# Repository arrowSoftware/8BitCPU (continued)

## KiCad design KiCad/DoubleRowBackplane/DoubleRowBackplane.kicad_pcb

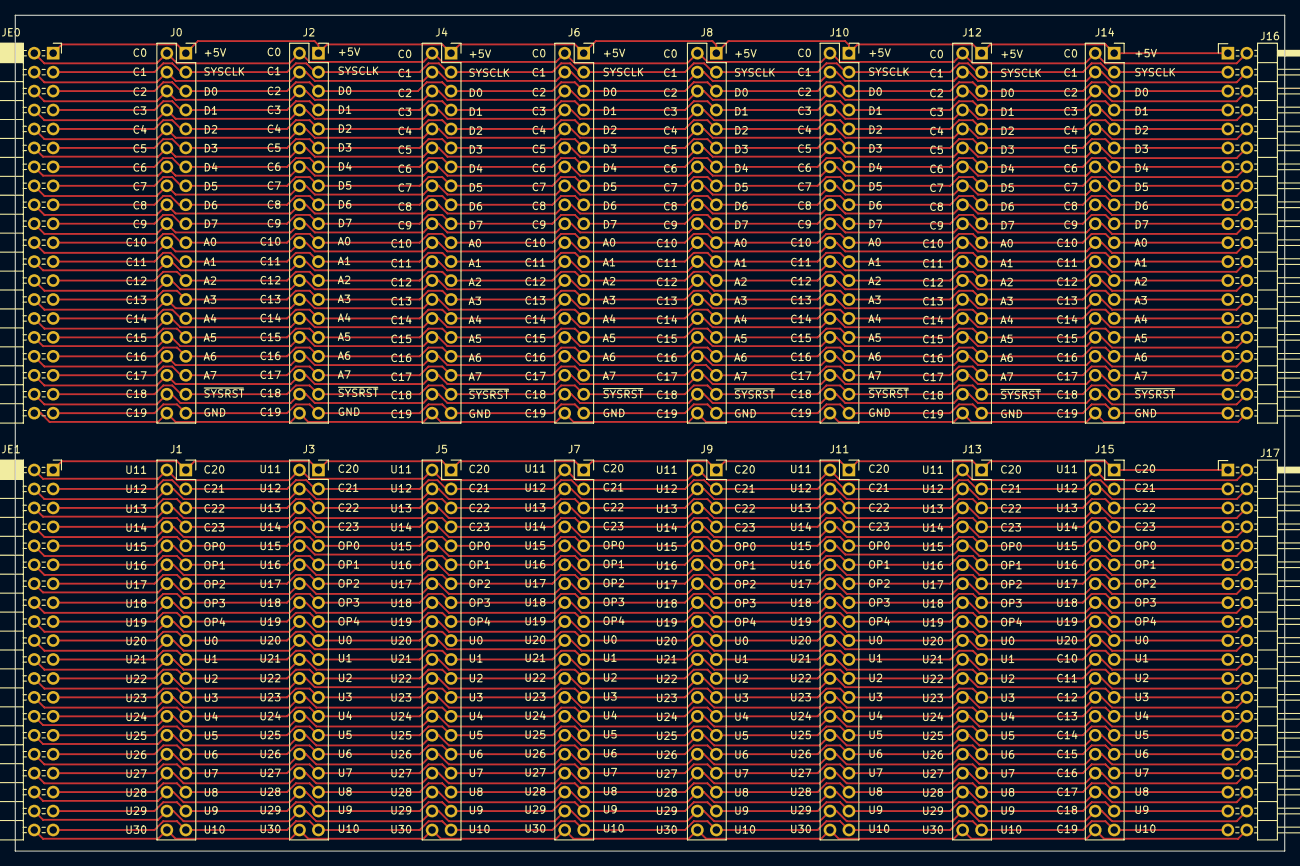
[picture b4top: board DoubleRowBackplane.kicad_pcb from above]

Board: 2 copper layers, 170.2 x 112.0 mm, 20 parts (0 on the bottom side), 80 nets.

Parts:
J0, J1, J2, J3, J4, J5, J6, J7, J8, J9, J10, J11, J12, J13, J14, J15: Conn_02x20_Row_Letter_First; PinSocket_2x20_P2.54mm_Vertical
J16, J17: Conn_02x20_Row_Letter_First; PinHeader_2x20_P2.54mm_Horizontal
JE0, JE1: Conn_02x20_Row_Letter_First; PinSocket_2x20_P2.54mm_Horizontal

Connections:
/+5V: J0.1, J2.1, J4.1, J6.1, J8.1, J10.1, J12.1, J14.1, J16.1, JE0.1
/A0: J0.21, J2.21, J4.21, J6.21, J8.21, J10.21, J12.21, J14.21, J16.21, JE0.21
/A1: J0.23, J2.23, J4.23, J6.23, J8.23, J10.23, J12.23, J14.23, J16.23, JE0.23
/A2: J0.25, J2.25, J4.25, J6.25, J8.25, J10.25, J12.25, J14.25, J16.25, JE0.25
/A3: J0.27, J2.27, J4.27, J6.27, J8.27, J10.27, J12.27, J14.27, J16.27, JE0.27
/A4: J0.29, J2.29, J4.29, J6.29, J8.29, J10.29, J12.29, J14.29, J16.29, JE0.29
/A5: J0.31, J2.31, J4.31, J6.31, J8.31, J10.31, J12.31, J14.31, J16.31, JE0.31
/A6: J0.33, J2.33, J4.33, J6.33, J8.33, J10.33, J12.33, J14.33, J16.33, JE0.33
/A7: J0.35, J2.35, J4.35, J6.35, J8.35, J10.35, J12.35, J14.35, J16.35, JE0.35
/C0: J0.2, J2.2, J4.2, J6.2, J8.2, J10.2, J12.2, J14.2, J16.2, JE0.2
/C1: J0.4, J2.4, J4.4, J6.4, J8.4, J10.4, J12.4, J14.4, J16.4, JE0.4
/C2: J0.6, J2.6, J4.6, J6.6, J8.6, J10.6, J12.6, J14.6, J16.6, JE0.6
/C3: J0.8, J2.8, J4.8, J6.8, J8.8, J10.8, J12.8, J14.8, J16.8, JE0.8
/C4: J0.10, J2.10, J4.10, J6.10, J8.10, J10.10, J12.10, J14.10, J16.10, JE0.10
/C5: J0.12, J2.12, J4.12, J6.12, J8.12, J10.12, J12.12, J14.12, J16.12, JE0.12
/C6: J0.14, J2.14, J4.14, J6.14, J8.14, J10.14, J12.14, J14.14, J16.14, JE0.14
/C7: J0.16, J2.16, J4.16, J6.16, J8.16, J10.16, J12.16, J14.16, J16.16, JE0.16
/C8: J0.18, J2.18, J4.18, J6.18, J8.18, J10.18, J12.18, J14.18, J16.18, JE0.18
/C9: J0.20, J2.20, J4.20, J6.20, J8.20, J10.20, J12.20, J14.20, J16.20, JE0.20
/C10: J0.22, J2.22, J4.22, J6.22, J8.22, J10.22, J12.22, J14.22, J16.22, JE0.22
/C11: J0.24, J2.24, J4.24, J6.24, J8.24, J10.24, J12.24, J14.24, J16.24, JE0.24
/C12: J0.26, J2.26, J4.26, J6.26, J8.26, J10.26, J12.26, J14.26, J16.26, JE0.26
/C13: J0.28, J2.28, J4.28, J6.28, J8.28, J10.28, J12.28, J14.28, J16.28, JE0.28
/C14: J0.30, J2.30, J4.30, J6.30, J8.30, J10.30, J12.30, J14.30, J16.30, JE0.30
/C15: J0.32, J2.32, J4.32, J6.32, J8.32, J10.32, J12.32, J14.32, J16.32, JE0.32
/C16: J0.34, J2.34, J4.34, J6.34, J8.34, J10.34, J12.34, J14.34, J16.34, JE0.34
/C17: J0.36, J2.36, J4.36, J6.36, J8.36, J10.36, J12.36, J14.36, J16.36, JE0.36
/C18: J0.38, J2.38, J4.38, J6.38, J8.38, J10.38, J12.38, J14.38, J16.38, JE0.38
/C19: J0.40, J2.40, J4.40, J6.40, J8.40, J10.40, J12.40, J14.40, J16.40, JE0.40
/C20: J1.1, J3.1, J5.1, J7.1, J9.1, J11.1, J13.1, J15.1, J17.1, JE1.1
/C21: J1.3, J3.3, J5.3, J7.3, J9.3, J11.3, J13.3, J15.3, J17.3, JE1.3
/C22: J1.5, J3.5, J5.5, J7.5, J9.5, J11.5, J13.5, J15.5, J17.5, JE1.5
/C23: J1.7, J3.7, J5.7, J7.7, J9.7, J11.7, J13.7, J15.7, J17.7, JE1.7
/D0: J0.5, J2.5, J4.5, J6.5, J8.5, J10.5, J12.5, J14.5, J16.5, JE0.5
/D1: J0.7, J2.7, J4.7, J6.7, J8.7, J10.7, J12.7, J14.7, J16.7, JE0.7
/D2: J0.9, J2.9, J4.9, J6.9, J8.9, J10.9, J12.9, J14.9, J16.9, JE0.9
/D3: J0.11, J2.11, J4.11, J6.11, J8.11, J10.11, J12.11, J14.11, J16.11, JE0.11
/D4: J0.13, J2.13, J4.13, J6.13, J8.13, J10.13, J12.13, J14.13, J16.13, JE0.13
/D5: J0.15, J2.15, J4.15, J6.15, J8.15, J10.15, J12.15, J14.15, J16.15, JE0.15
/D6: J0.17, J2.17, J4.17, J6.17, J8.17, J10.17, J12.17, J14.17, J16.17, JE0.17
/D7: J0.19, J2.19, J4.19, J6.19, J8.19, J10.19, J12.19, J14.19, J16.19, JE0.19
/GND: J0.39, J2.39, J4.39, J6.39, J8.39, J10.39, J12.39, J14.39, J16.39, JE0.39
/OP0: J1.9, J3.9, J5.9, J7.9, J9.9, J11.9, J13.9, J15.9, J17.9, JE1.9
/OP1: J1.11, J3.11, J5.11, J7.11, J9.11, J11.11, J13.11, J15.11, J17.11, JE1.11
/OP2: J1.13, J3.13, J5.13, J7.13, J9.13, J11.13, J13.13, J15.13, J17.13, JE1.13
/OP3: J1.15, J3.15, J5.15, J7.15, J9.15, J11.15, J13.15, J15.15, J17.15, JE1.15
/OP4: J1.17, J3.17, J5.17, J7.17, J9.17, J11.17, J13.17, J15.17, J17.17, JE1.17
/SYSCLK: J0.3, J2.3, J4.3, J6.3, J8.3, J10.3, J12.3, J14.3, J16.3, JE0.3
/U0: J1.19, J3.19, J5.19, J7.19, J9.19, J11.19, J13.19, J15.19, J17.19, JE1.19
/U1: J1.21, J3.21, J5.21, J7.21, J9.21, J11.21, J13.21, J15.21, J17.21, JE1.21
/U2: J1.23, J3.23, J5.23, J7.23, J9.23, J11.23, J13.23, J15.23, J17.23, JE1.23
/U3: J1.25, J3.25, J5.25, J7.25, J9.25, J11.25, J13.25, J15.25, J17.25, JE1.25
/U4: J1.27, J3.27, J5.27, J7.27, J9.27, J11.27, J13.27, J15.27, J17.27, JE1.27
/U5: J1.29, J3.29, J5.29, J7.29, J9.29, J11.29, J13.29, J15.29, J17.29, JE1.29
/U6: J1.31, J3.31, J5.31, J7.31, J9.31, J11.31, J13.31, J15.31, J17.31, JE1.31
/U7: J1.33, J3.33, J5.33, J7.33, J9.33, J11.33, J13.33, J15.33, J17.33, JE1.33
/U8: J1.35, J3.35, J5.35, J7.35, J9.35, J11.35, J13.35, J15.35, J17.35, JE1.35
/U9: J1.37, J3.37, J5.37, J7.37, J9.37, J11.37, J13.37, J15.37, J17.37, JE1.37
/U10: J1.39, J3.39, J5.39, J7.39, J9.39, J11.39, J13.39, J15.39, J17.39, JE1.39
/U11: J1.2, J3.2, J5.2, J7.2, J9.2, J11.2, J13.2, J15.2, J17.2, JE1.2
/U12: J1.4, J3.4, J5.4, J7.4, J9.4, J11.4, J13.4, J15.4, J17.4, JE1.4
/U13: J1.6, J3.6, J5.6, J7.6, J9.6, J11.6, J13.6, J15.6, J17.6, JE1.6
/U14: J1.8, J3.8, J5.8, J7.8, J9.8, J11.8, J13.8, J15.8, J17.8, JE1.8
/U15: J1.10, J3.10, J5.10, J7.10, J9.10, J11.10, J13.10, J15.10, J17.10, JE1.10
/U16: J1.12, J3.12, J5.12, J7.12, J9.12, J11.12, J13.12, J15.12, J17.12, JE1.12
/U17: J1.14, J3.14, J5.14, J7.14, J9.14, J11.14, J13.14, J15.14, J17.14, JE1.14
/U18: J1.16, J3.16, J5.16, J7.16, J9.16, J11.16, J13.16, J15.16, J17.16, JE1.16
/U19: J1.18, J3.18, J5.18, J7.18, J9.18, J11.18, J13.18, J15.18, J17.18, JE1.18
/U20: J1.20, J3.20, J5.20, J7.20, J9.20, J11.20, J13.20, J15.20, J17.20, JE1.20
/U21: J1.22, J3.22, J5.22, J7.22, J9.22, J11.22, J13.22, J15.22, J17.22, JE1.22
/U22: J1.24, J3.24, J5.24, J7.24, J9.24, J11.24, J13.24, J15.24, J17.24, JE1.24
/U23: J1.26, J3.26, J5.26, J7.26, J9.26, J11.26, J13.26, J15.26, J17.26, JE1.26
/U24: J1.28, J3.28, J5.28, J7.28, J9.28, J11.28, J13.28, J15.28, J17.28, JE1.28
/U25: J1.30, J3.30, J5.30, J7.30, J9.30, J11.30, J13.30, J15.30, J17.30, JE1.30
/U26: J1.32, J3.32, J5.32, J7.32, J9.32, J11.32, J13.32, J15.32, J17.32, JE1.32
/U27: J1.34, J3.34, J5.34, J7.34, J9.34, J11.34, J13.34, J15.34, J17.34, JE1.34
/U28: J1.36, J3.36, J5.36, J7.36, J9.36, J11.36, J13.36, J15.36, J17.36, JE1.36
/U29: J1.38, J3.38, J5.38, J7.38, J9.38, J11.38, J13.38, J15.38, J17.38, JE1.38
/U30: J1.40, J3.40, J5.40, J7.40, J9.40, J11.40, J13.40, J15.40, J17.40, JE1.40
/~SYSRST: J0.37, J2.37, J4.37, J6.37, J8.37, J10.37, J12.37, J14.37, J16.37, JE0.37

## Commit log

2023-09-28 Adding base logism circuits
2023-09-29 Adding 1/8 bit registers
2023-09-29 Adding registers and alu to main circuit
2023-09-29 Adding output register
2023-09-29 Adding reverser
2023-09-30 fixing wierd bug
2023-09-30 updating read me and adding images
2023-09-30 adding program counter and readme updates
2023-10-01 Adding SRAM
2023-10-01 Debugging SRAM
2023-10-01 Fixing SRAM 256
2023-10-01 Adding program loader
2023-10-01 Adding clock c++ code
2023-10-02 Adding rom
2023-10-02 Finishing th instruction decoder
2023-10-03 Creating rom file, debugging opcodes
2023-10-04 testing digital
2023-10-04 cleanup
2023-10-05 Adding emulator code and updating processor layout
2023-10-05 Adding emualtion files
2023-10-05 Adding dlatch and d flip flop, adding makefile
2023-10-05 Working dflip flop
2023-10-06 Testing dflipflop
2023-10-06 fixed dflip
2023-10-06 Making a different emulator
2023-10-07 Adding ROM, RAM, program loader
2023-10-07 Fixing test name
2023-10-07 removing test.exe
2023-10-07 Adding RAM test and rom test updates
2023-10-08 Testing the cpu and updating readme
2023-10-11 updating instructions on readme
2023-10-11 Dont remember the change
2023-10-11 Adding table temps
2023-10-11 Auto table
2023-10-11 Updating instruction table
2023-10-11 Fixing extra flags
2023-10-11 Testing center image
2023-10-11 Adding skeleton for the instruction testing
2023-10-12 Adding test gifs and updating readme
2023-10-12 Adding B register tests
2023-10-13 testing ADD logic and fixing ROM, ALU sel connections
2023-10-13 Testing SUB logic
2023-10-13 Adding instruction decorer base
2023-10-14 Testing out logic and using logisim registers becauase propagations issues
2023-10-14 Testing jump logic
2023-10-15 Testing jumps, fibinacci and multiplication
2023-10-15 Updating the README for the reamining items
2023-10-16 Adding reference for custom asm
2023-10-16 Adding assembler and adding reference to readme
2023-10-17 Updating assembler
2023-10-17 Unit testing assembler
2023-10-18 Wdding unit tests for labels and allowing incase sensitivity
2023-10-18 Finishing unit testing output, updating makefile for both test and target flags
2023-10-18 Adding windows,unix deletes
2023-10-18 Updating main.cpp to abort if no file and updating readme for assembler
2023-10-18 Updating readme
2023-10-18 Update README.md
    fix lable spelling mistake
2023-10-19 Adding objdump
2023-10-26 Removing digital
2023-10-26 Updating objdump
2023-10-30 changing to cmake
2023-10-30 Adding objdump output
2023-10-30 updating the emulator for alu and instruction decortder"
2023-11-02 Adding the instruction microcode decoder file read
2023-11-11 Updating instruction deocrder emulator and kicad schematics
2023-11-14 Adding 6 slot backplane files
2023-11-14 adding backplane references
2023-11-14 adding pcb layouts for clock module
